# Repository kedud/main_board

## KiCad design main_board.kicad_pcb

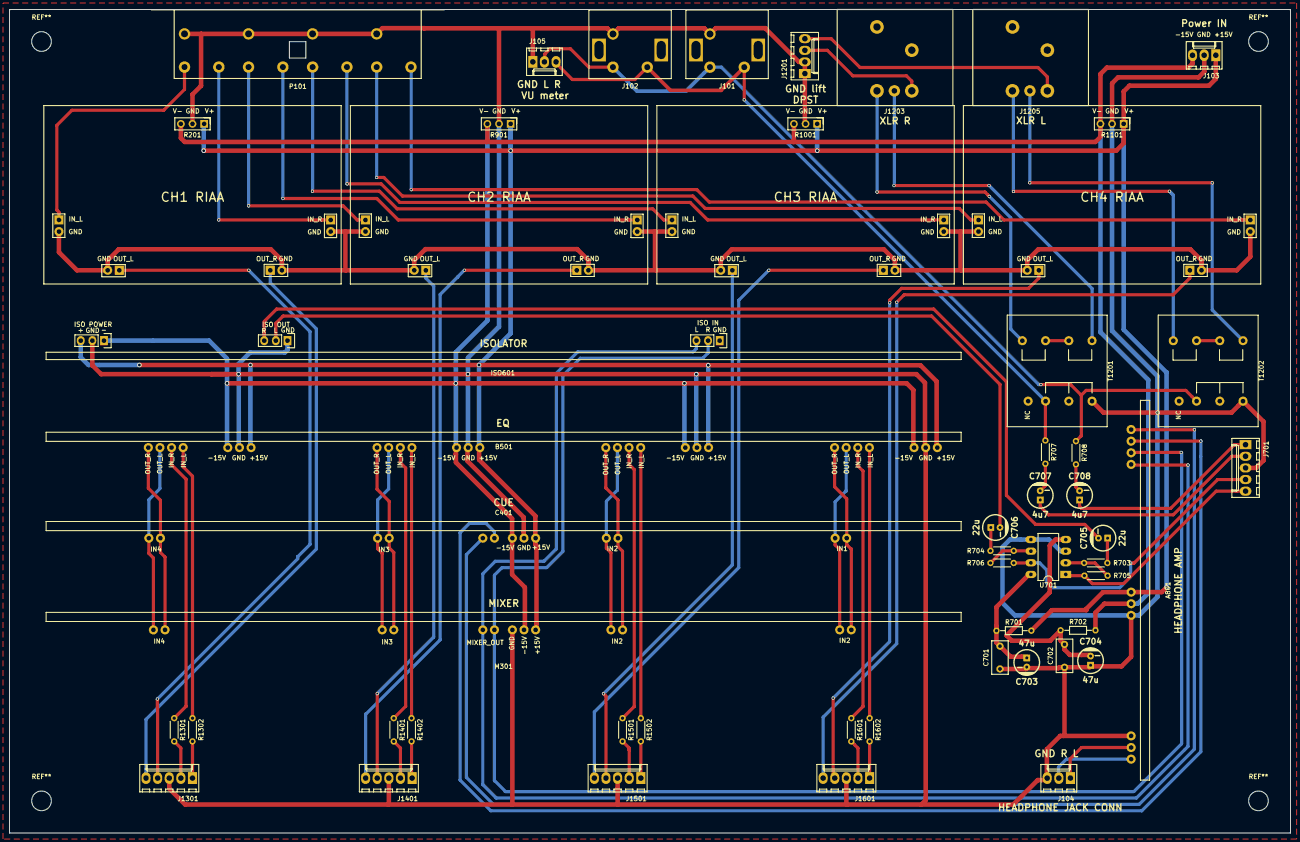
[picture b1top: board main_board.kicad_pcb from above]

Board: 2 copper layers, 280.0 x 180.0 mm, 50 parts (0 on the bottom side), 73 nets.

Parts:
A801: hp_amp; HP_amp
B501: Baxandall
C401: Cue; cue_footprint
C701, C702: 100n; C_Rect_L7.2mm_W3.5mm_P5.00mm_FKS2_FKP2_MKS2_MKP2
C703, C704: 47u; CP_5x11mm
C705, C706: 22u; CP_5x11mm
C707, C708: 4u7; CP_5x11mm
ISO601: ISO; ISO_footprint
J101, J102: Conn_Coaxial_x2; PJRAS1X2S01AUX
J103, J104, J105: Conn_01x03_Male; Molex_KK-6410-03_03x2.54mm_Straight
J701, J1301, J1401, J1501, J1601: Conn_01x05_Male; Molex_KK-6410-05_05x2.54mm_Straight
J1201: Conn_01x04_Male; Molex_KK-6410-04_04x2.54mm_Straight
J1203, J1205: XLR3; Neutrik_NC3MAAH-0
M301: Mixer; mixer_footprint
P101: PJRAS4X2U01AUX
R201, R901, R1001, R1101: RIAA_stereo; RIAA_footprint
R701, R702: 100; R_Axial_DIN0204_L3.6mm_D1.6mm_P7.62mm_Horizontal
R703, R704: 10K; R_Axial_DIN0204_L3.6mm_D1.6mm_P5.08mm_Horizontal
R705, R706: 12K; R_Axial_DIN0204_L3.6mm_D1.6mm_P5.08mm_Horizontal
R707, R708: R_Small; R_Axial_DIN0204_L3.6mm_D1.6mm_P5.08mm_Horizontal
R1301, R1302, R1401, R1402, R1501, R1502, R1601, R1602: 100K; R_Axial_DIN0204_L3.6mm_D1.6mm_P5.08mm_Horizontal
T1201, T1202: Transformer_SP_2S; Transf_audio_1P2S
U701: NE5532; DIP-8_W7.62mm_LongPads

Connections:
/ASYM_OUT_L: J101.2, J102.2, J105.2, R708.1, T1202.1
/ASYM_OUT_R: J101.1, J102.1, J105.3, R707.1, T1201.1
/BO1_L: B501.6, C401.4, M301.4
/BO1_R: B501.7, C401.5, M301.5
/BO2_L: B501.13, C401.6, M301.6
/BO2_R: B501.14, C401.7, M301.7
/BO3_L: B501.20, C401.8, M301.8
/BO3_R: B501.21, C401.9, M301.9
/BO4_L: B501.27, C401.10, M301.10
/BO4_R: B501.28, C401.11, M301.11
/CUE_OUT_L: A801.6, C401.13
/CUE_OUT_R: A801.7, C401.12
/ISO_OUT_L: C706.2, ISO601.5
/ISO_OUT_R: C705.2, ISO601.4
/MIX_OUT_L: A801.4, ISO601.7, M301.12
/MIX_OUT_R: A801.5, ISO601.8, M301.13
/PO1_L: J1301.4, R201.7
/PO1_R: J1301.5, R201.8
/PO2_L: J1401.4, R901.7
/PO2_R: J1401.5, R901.8
/PO3_L: J1501.4, R1001.7
/PO3_R: J1501.5, R1001.8
/PO4_L: J1601.4, R1101.7
/PO4_R: J1601.5, R1101.8
/TO1_L: B501.4, R1302.1
/TO1_R: B501.5, R1301.1
/TO2_L: B501.11, R1402.1
/TO2_R: B501.12, R1401.1
/TO3_L: B501.18, R1502.1
/TO3_R: B501.19, R1501.1
/TO4_L: B501.25, R1602.1
/TO4_R: B501.26, R1601.1
/V+: A801.1, B501.1, B501.8, B501.15, B501.22, C401.1, ISO601.1, J103.1, M301.1, R201.1, R701.2, R901.1, R1001.1, R1101.1
/V-: A801.3, B501.3, B501.10, B501.17, B501.24, C401.3, ISO601.3, J103.3, M301.3, R201.3, R702.2, R901.3, R1001.3, R1101.3
/headphone_preamp/OUT_L: A801.9, J104.1
/headphone_preamp/OUT_R: A801.10, J104.2
/master/+15V: C701.2, C703.1, R701.1, U701.8
/master/-15V: C702.2, C704.2, R702.1, U701.4
/master/MIX_OUT_L: C708.1, J701.1
/master/MIX_OUT_R: C707.1, J701.2
/master/PRE_MIX_L: J701.4, R706.1, U701.7
/master/PRE_MIX_R: J701.5, R705.1, U701.1
/preamp_1/Left_input: P101.T2D, R201.4
/preamp_1/Right_input: P101.T1D, R201.11
/preamp_2/Left_input: P101.T2C, R901.4
/preamp_2/Right_input: P101.T1C, R901.11
/preamp_3/Left_input: P101.T2B, R1001.4
/preamp_3/Right_input: P101.T1B, R1001.11
/preamp_4/Left_input: P101.T2A, R1101.4
/preamp_4/Right_input: P101.T1A, R1101.11
/symetriseur/XLR_GND_L: J1201.4, J1205.1
/symetriseur/XLR_GND_R: J1201.3, J1203.1
/trim_1/POT_OUT_L: J1301.1, R1302.2
/trim_1/POT_OUT_R: J1301.2, R1301.2
/trim_2/POT_OUT_L: J1401.1, R1402.2
/trim_2/POT_OUT_R: J1401.2, R1401.2
/trim_3/POT_OUT_L: J1501.1, R1502.2
/trim_3/POT_OUT_R: J1501.2, R1501.2
/trim_4/POT_OUT_L: J1601.1, R1602.2
/trim_4/POT_OUT_R: J1601.2, R1601.2
GND: A801.2, A801.8, B501.2, B501.9, B501.16, B501.23, C401.2, C701.1, C702.1, C703.2, C704.1, ISO601.2, ISO601.6, ISO601.9, J101.3, J102.3, J103.2, J104.3, J105.1, J701.3, J1201.1, J1201.2, J1301.3, J1401.3, J1501.3, J1601.3, M301.2, P101.SA, P101.SB, P101.SC, P101.SD, R201.2, R201.5, R201.6, R201.9, R201.10, R901.2, R901.5, R901.6, R901.9, R901.10, R1001.2, R1001.5, R1001.6, R1001.9, R1001.10, R1101.2, R1101.5, R1101.6, R1101.9, R1101.10, T1201.3, T1202.3, U701.3, U701.5
unnamed: C705.1, R703.2
unnamed: C706.1, R704.2
unnamed: C707.2, R707.2
unnamed: C708.2, R708.2
unnamed: J1203.2, T1201.7
unnamed: J1203.3, T1201.4
unnamed: J1205.2, T1202.7
unnamed: J1205.3, T1202.4
unnamed: R703.1, R705.2, U701.2
unnamed: R704.1, R706.2, U701.6
unnamed: T1201.5, T1201.6
unnamed: T1202.5, T1202.6

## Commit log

2018-11-28 Finished layout
2018-11-29 Update silkscreen on RIAA footprints
